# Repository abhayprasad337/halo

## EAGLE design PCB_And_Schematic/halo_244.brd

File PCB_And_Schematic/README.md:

This folder includes schematics and pcb deisgns which are part of this project.

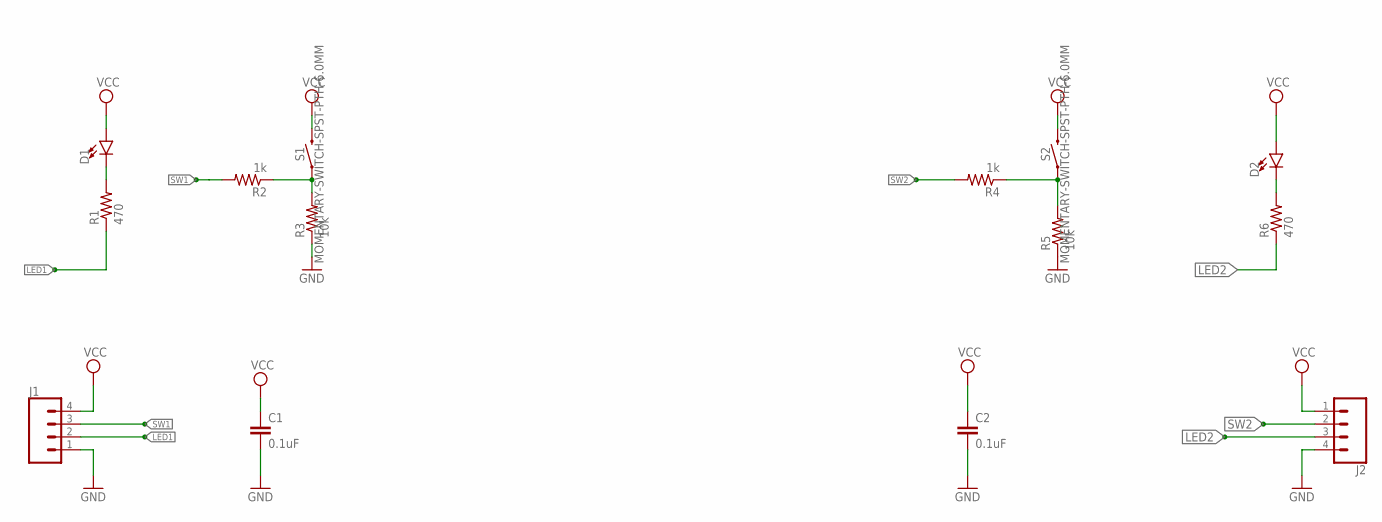
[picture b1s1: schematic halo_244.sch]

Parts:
C1, C2: 0.1uF; CAP-PTH-SMALL-KIT
D1, D2: LED-3MM-NO_SILK; LED_3MM-NS
J1, J2: CONN_04; 1X04
R1, R6: 470; 0207/12; MPN MCF 0.25W 470R
R2, R4: 1k; 0207/12
R3, R5: 10k; 0207/12; MPN MCF 0.25W 10K
S1, S2: MOMENTARY-SWITCH-SPST-PTH-6.0MM; TACTILE_SWITCH_PTH_6.0MM

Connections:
GND: C1.2, C2.2, J1.1, J2.4, R3.1, R5.1
LED1: J1.2, R1.1
LED2: J2.3, R6.1
unnamed: R2.1, R3.2, S1.1
unnamed: D1.K (C), R1.2
unnamed: D2.K (C), R6.2
unnamed: R4.1, R5.2, S2.1
SW1: J1.3, R2.2
SW2: J2.2, R4.2
VCC: C1.1, C2.1, D1.A, D2.A, J1.4, J2.1, S1.3 (2), S2.3 (2)

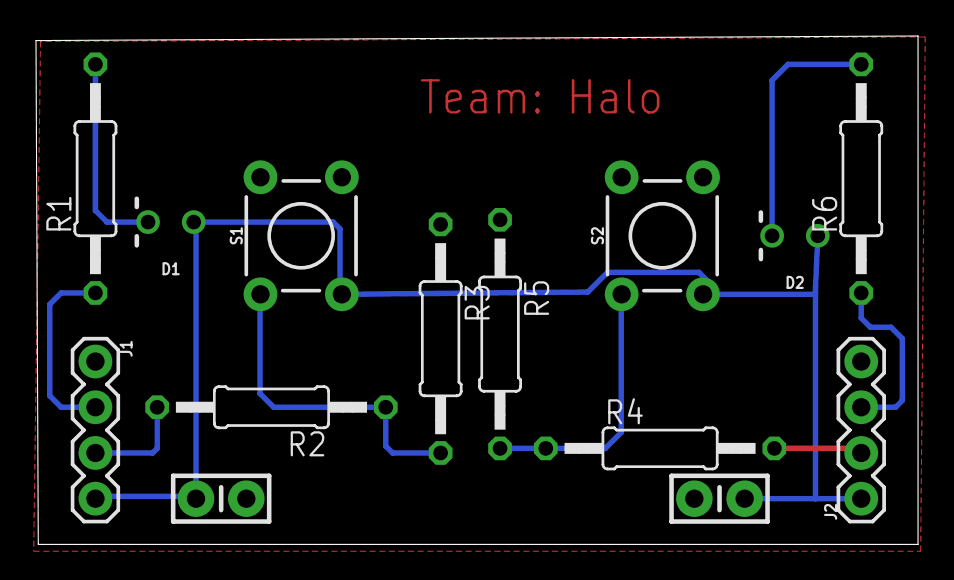
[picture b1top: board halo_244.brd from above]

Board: 2 copper layers, 49.0 x 28.2 mm, 14 parts (0 on the bottom side), 10 nets.

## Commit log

2017-04-09 initialCommit
2017-04-14 motion analysis 1) debug_e.h Has the basic LOGGING functions that we shall use throughout the project. This will help us later to take out all the logs before release by just undefining a macro: say,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
2017-04-20 added README
2017-04-20 initial_schematic_and_pcb_design
2017-04-24 Added ultrasonic sensor interface
2017-04-25 reduced the size of board
2017-05-01 added support for SW start/stop logging
2017-05-01 Updated code for data logging from accelerometer
2017-05-03 final pcb files
2017-05-14 Modified files to support integration
2017-05-14 USS Module integration
2017-05-15 adding uio apis implementations
2017-05-16 halo_uio linker error fix
2017-05-16 Build error resolve
2017-05-17 added new wci source file
2017-05-19 Added ADA interface and modules. Other changes are all minor.
2017-05-20 1. DEBUG header changed ; use LOGV, LOGD instead of printfs/u0_dbg_printf for debugging 2. HALO API change in WCI and ADA 3. fixes in UIO, MAE and USS 4. WHI + WCI tested working 5. in main.cpp defin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
2017-05-20 halo glue code commit
2017-05-20 ADA, UIO includes all LEDs and components as per design; MAE tweaked; USS debugged - now using HW timer instead of sys_gettime_us
2017-05-22 Updated MAE algorithm!
2017-05-22 MAE minor bug fix.
2017-05-23 USS: Commented debug prints

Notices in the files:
parts and their libraries:
SparkFun-Capacitors: Licensing: Creative Commons ShareAlike 4.0 International - https://creativecommons.org/licenses/by-sa/4.0
